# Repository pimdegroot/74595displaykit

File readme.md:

# 74595 display PMOD assembly instructions

## Introduction

This are the assembly instructions for the 74595 display PMOD. It is a led display using a shift register to drive the columns and 4 mosfets to drain the rows. Driving the display is quite similar to the large RGB led panels.

## Step 1

Check if you have all the parts.

* 32x LED
* 8x 110R resistor
* 4x 2n7002 mosfet
* 1x 100nF capacitor
* 1x 74HC595 shift register
* 1x 2x6 male angled header
* 1x PCB

You also need some tools. Reccomended are:

* Soldering Iron
* Tweezers
* Fine solder (0.5mm diameter)

## Step 2

Solder the LEDs. They should go on the large angled pads with a U shaped silkscreen. First apply solder to the pad closest to the side where you hold your soldering iron. 

The LEDs are directional. There is an arrow on the bottom and a green dot on the top of the component, this should point downward towards the white line under the pads. Solder one side and then the other.

Using your tweezers solder one of the sides of your led. When it is fixed, solder the other side. Repeat 31 times.

## Step 3

Solder the resistors. The soldering method is the same as step 2, except that the resistors are not directional, which means orientation doesnt matter.

## Step 4

Solder the capacitor to the pads marked C1. There are also pads for a larger capacitor, but tests showed that this one is not needed.

## Step 5

Solder the mosfets. The trick here is to apply solder to the single pad on one side of the mosfet and solder the other two when the component is placed.

## Step 6

Solder the 74HC595 chip. Solder pad 1 first. Pin one is marked with a dot on the chip, and a longer line at the U1 mark on the board. Make sure that the allignment of the pins is correct for all the pads. Then solder all the other pins.

## Step 7

Solder the header. First fix one pin and using a tweezer adjust alignment as needed. Then solder all the other pins.

## Step 8

Test the display. In the examples there is code for an arduino, STM32 and Icebreaker.

With the connector left, led (0,0) is top left and led (8,3) is bottom right.

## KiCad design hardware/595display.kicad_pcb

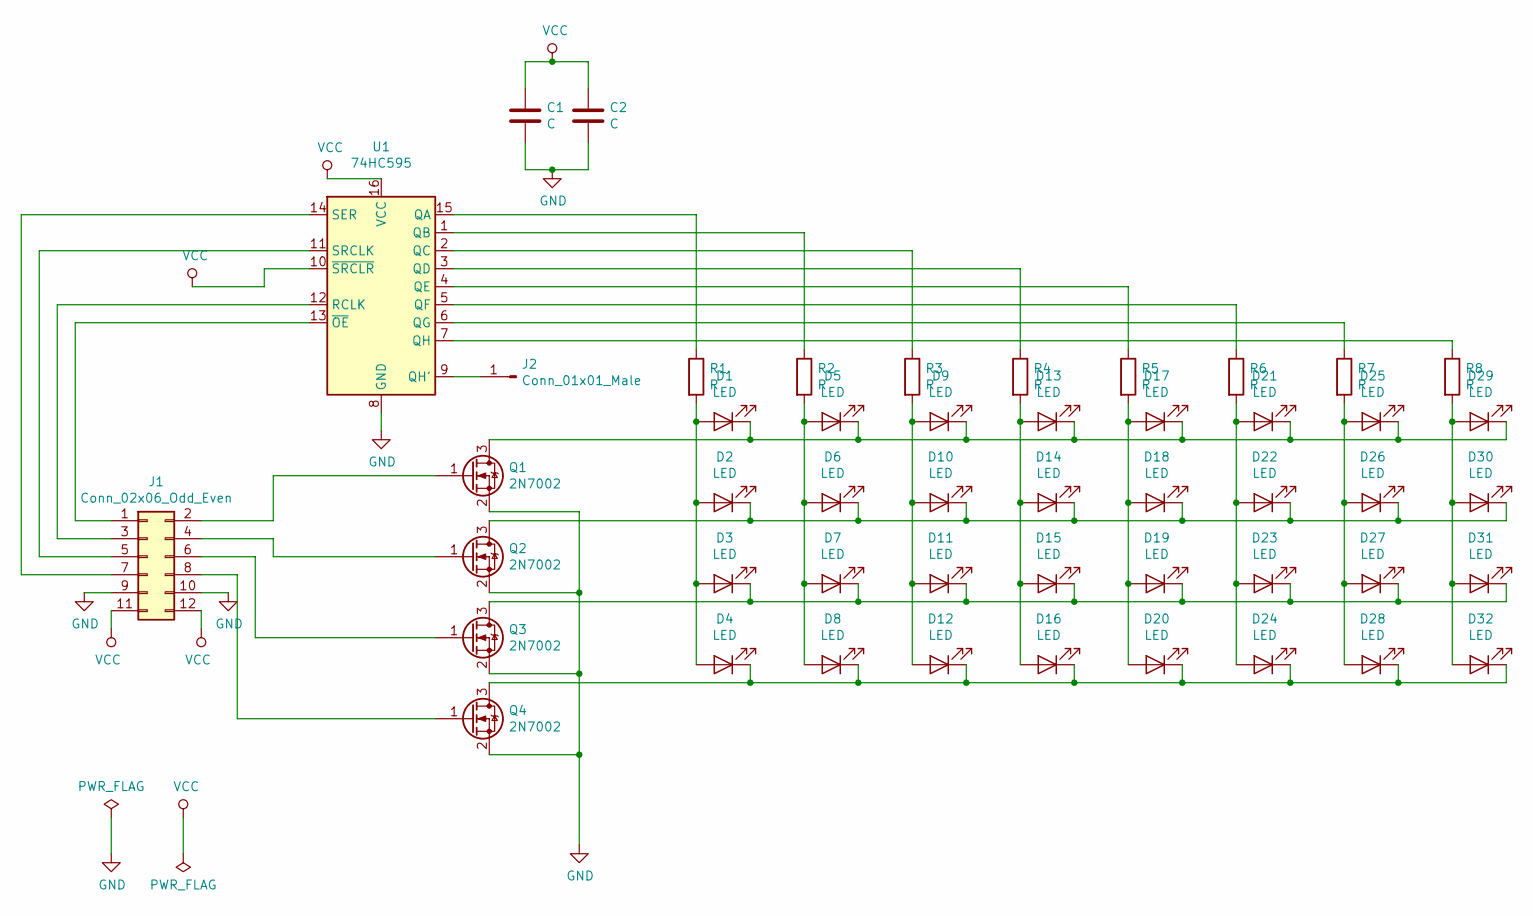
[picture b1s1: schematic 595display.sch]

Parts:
C1: C; C_0805_2012Metric
C2: C; C_1206_3216Metric
D1, D2, D3, D4, D5, D6, D7, D8, D9, D10, D11, D12, D13, D14, D15, D16, D17, D18, D19, D20, D21, D22, D23, D24, D25, D26, D27, D28, D29, D30, D31, D32: LED; LED_1206_3216Metric
J1: Conn_02x06_Odd_Even; PinHeader_2x06_P2.54mm_Vertical
J2: Conn_01x01_Male; PinHeader_1x01_P2.54mm_Vertical
Q1, Q2, Q3, Q4: 2N7002; SOT-23
R1, R2, R3, R4, R5, R6, R7, R8: R; R_0805_2012Metric
U1: 74HC595; SOIC-16_3.9x9.9mm_P1.27mm

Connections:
GND: C1.2, C2.2, J1.9, J1.10, Q1.2 (S), Q2.2 (S), Q3.2 (S), Q4.2 (S), U1.8 (GND)
unnamed: D1.1 (K), D5.1 (K), D9.1 (K), D13.1 (K), D17.1 (K), D21.1 (K), D25.1 (K), D29.1 (K), Q1.3 (D)
unnamed: D1.2 (A), D2.2 (A), D3.2 (A), D4.2 (A), R1.2
unnamed: D5.2 (A), D6.2 (A), D7.2 (A), D8.2 (A), R2.2
unnamed: D2.1 (K), D6.1 (K), D10.1 (K), D14.1 (K), D18.1 (K), D22.1 (K), D26.1 (K), D30.1 (K), Q2.3 (D)
unnamed: D9.2 (A), D10.2 (A), D11.2 (A), D12.2 (A), R3.2
unnamed: D3.1 (K), D7.1 (K), D11.1 (K), D15.1 (K), D19.1 (K), D23.1 (K), D27.1 (K), D31.1 (K), Q3.3 (D)
unnamed: D4.1 (K), D8.1 (K), D12.1 (K), D16.1 (K), D20.1 (K), D24.1 (K), D28.1 (K), D32.1 (K), Q4.3 (D)
unnamed: D13.2 (A), D14.2 (A), D15.2 (A), D16.2 (A), R4.2
unnamed: D17.2 (A), D18.2 (A), D19.2 (A), D20.2 (A), R5.2
unnamed: D21.2 (A), D22.2 (A), D23.2 (A), D24.2 (A), R6.2
unnamed: D25.2 (A), D26.2 (A), D27.2 (A), D28.2 (A), R7.2
unnamed: D29.2 (A), D30.2 (A), D31.2 (A), D32.2 (A), R8.2
unnamed: J1.1, U1.13 (~OE)
unnamed: J1.2, Q1.1 (G)
unnamed: J1.3, U1.12 (RCLK)
unnamed: J1.4, Q2.1 (G)
unnamed: J1.5, U1.11 (SRCLK)
unnamed: J1.6, Q3.1 (G)
unnamed: J1.7, U1.14 (SER)
unnamed: J1.8, Q4.1 (G)
unnamed: J2.1, U1.9 (QH')
unnamed: R1.1, U1.15 (QA)
unnamed: R2.1, U1.1 (QB)
unnamed: R3.1, U1.2 (QC)
unnamed: R4.1, U1.3 (QD)
unnamed: R5.1, U1.4 (QE)
unnamed: R6.1, U1.5 (QF)
unnamed: R7.1, U1.6 (QG)
unnamed: R8.1, U1.7 (QH)
VCC: C1.1, C2.1, J1.11, J1.12, U1.10 (~SRCLR), U1.16 (VCC)

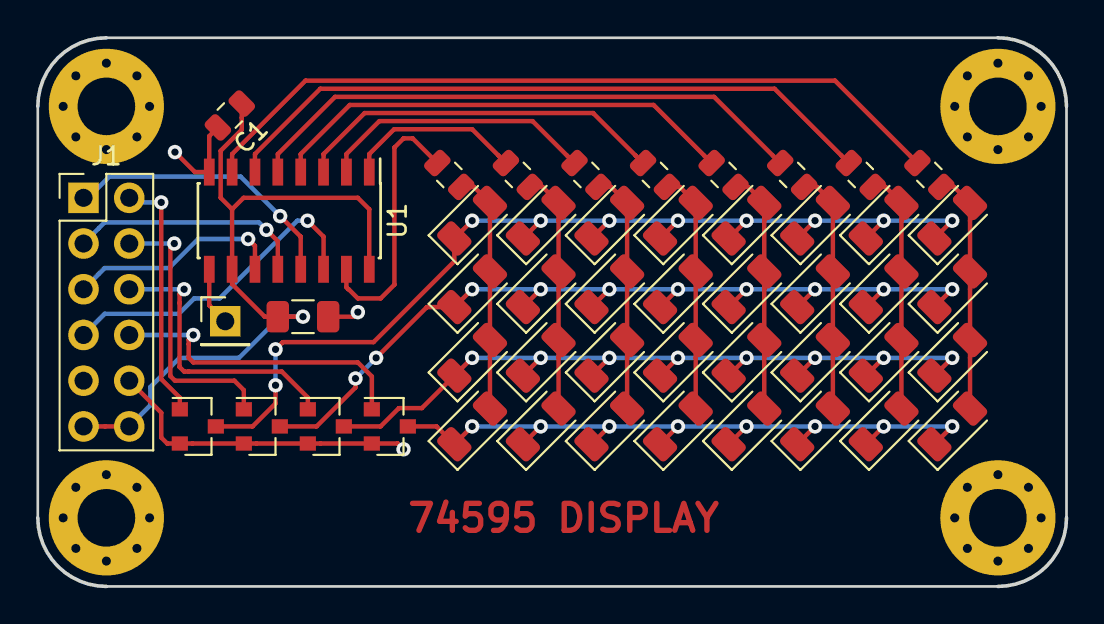
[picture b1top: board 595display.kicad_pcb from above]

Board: 2 copper layers, 57.2 x 30.5 mm, 49 parts (0 on the bottom side), 31 nets.
